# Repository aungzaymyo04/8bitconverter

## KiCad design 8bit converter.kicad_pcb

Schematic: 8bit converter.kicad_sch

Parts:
C1, C2: 10uf; CAP1608m
C19, C20, C21, C22, C23, C24, C25, C26, C27, C28, C29, C30, C31, C32, C33, C34, C35, C36: 0.1uF; CAP1608m
C37, C38: 10uF; CAP1608m
CN1: 10220-55G3PC
CN2: B4B-XH-A
D1: RB496EATR; Mouser Part Number 755-RB496EATR
D2, D3, D4, D5, D6, D7, D8, D9, D10: 1SS226
J1: CONBNC002
JP1: PAD_Short
MH1, MH2, MH3, MH4: HOLE_M3
PS1: MGS151205; Mouser Part Number 436-MGS151205
R2, R3, R5: 2.2k; REG1608m
R4, R6, R7, R8, R9, R10, R11, R12, R13: 10k; REG1608m
SW1: PN11SHNA03QE
U1, U2, U3, U4, U5, U6, U7, U8, U9: SN74LV1T34DBVR
U10: SC0915

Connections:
+3.3V: R2.2, R3.2, R5.2, U10.36 (3V3_OUT)
+5V: C19.2, C20.2, C21.2, C22.1, C23.2, C24.2, C25.1, C26.1, C27.2, C28.1, C29.2, C30.1, C31.2, C32.1, C33.2, C34.1, C35.2, C36.1, C37.1, C38.1, CN2.3, D1.4 (K_2), D2.2, D3.2, D4.2, D5.2, D6.2, D7.2, D8.2, D9.2, D10.2, PS1.4 (+VOUT), U1.5 (VCC), U2.5 (VCC), U3.5 (VCC), U4.5 (VCC), U5.5 (VCC), U6.5 (VCC), U7.5 (VCC), U8.5 (VCC), U9.5 (VCC), U10.39 (VSYS)
/+12V: C1.2, C2.2, CN1.9, CN1.19, PS1.3 (+VIN)
/SCL: CN2.2, R5.1, U10.32 (GP27)
/SDA: CN2.1, R3.1, U10.31 (GP26)
/o_5V_MUX0: CN1.14, D2.3, U1.4 (Y)
/o_5V_MUX1: CN1.4, D3.3, U2.4 (Y)
/o_5V_MUX2: CN1.13, D4.3, U3.4 (Y)
/o_5V_MUX3: CN1.3, D5.3, U4.4 (Y)
/o_5V_MUX4: CN1.12, D6.3, U5.4 (Y)
/o_5V_MUX5: CN1.2, D7.3, U6.4 (Y)
/o_5V_MUX6: CN1.11, D8.3, U7.4 (Y)
/o_5V_MUX7: CN1.1, D9.3, U8.4 (Y)
/o_MUX0: R8.1, U1.2 (A), U10.1 (GP0(UART_TX))
/o_MUX1: R6.1, U2.2 (A), U10.2 (GP1(UART_RX))
/o_MUX2: R4.1, U3.2 (A), U10.4 (GP2(SPI0_SCK))
/o_MUX3: R7.1, U4.2 (A), U10.5 (GP3(SPI0_TX))
/o_MUX4: R9.1, U5.2 (A), U10.6 (GP4(SPI0_RX)(UART1TX))
/o_MUX5: R10.1, U6.2 (A), U10.7 (GP5(SPI0CSn)(UART1RX))
/o_MUX6: R11.1, U7.2 (A), U10.9 (GP6(UART_TX))
/o_MUX7: R12.1, U8.2 (A), U10.10 (GP7(UART_RX))
/o_TRIG: R13.1, U9.2 (A), U10.11 (GP8(I2C1_SDA))
/o_TRIG_BNC: D10.3, J1.1, U9.4 (Y)
GND: C1.1, C2.1, C19.1, C20.1, C21.1, C22.2, C23.1, C24.1, C25.2, C26.2, C27.1, C28.2, C29.1, C30.2, C31.1, C32.2, C33.1, C34.2, C35.1, C36.2, C37.2, C38.2, CN1.7, CN1.17, CN1.MH1, CN1.MH2, CN2.4, D2.1, D3.1, D4.1, D5.1, D6.1, D7.1, D8.1, D9.1, D10.1, J1.2, J1.S1, J1.S2, JP1.1, MH1.1 (1_1), MH2.1 (1_1), MH3.1 (1_1), MH4.1 (1_1), PS1.2 (-VIN), PS1.6 (-VOUT), R4.2, R6.2, R7.2, R8.2, R9.2, R10.2, R11.2, R12.2, R13.2, SW1.1 (NO), U1.3 (GND), U2.3 (GND), U3.3 (GND), U4.3 (GND), U5.3 (GND), U6.3 (GND), U7.3 (GND), U8.3 (GND), U9.3 (GND), U10.3 (GND), U10.8 (GND), U10.13 (GND), U10.18 (GND), U10.23 (GND), U10.28 (GND), U10.33 (AGND), U10.38 (GND), U10.D2 (GND)
unnamed: D1.3 (A_2), U10.40 (VBUS)
unnamed: JP1.2, PS1.1 (RC)
unnamed: R2.1, SW1.2 (COM), U10.21 (GP16)

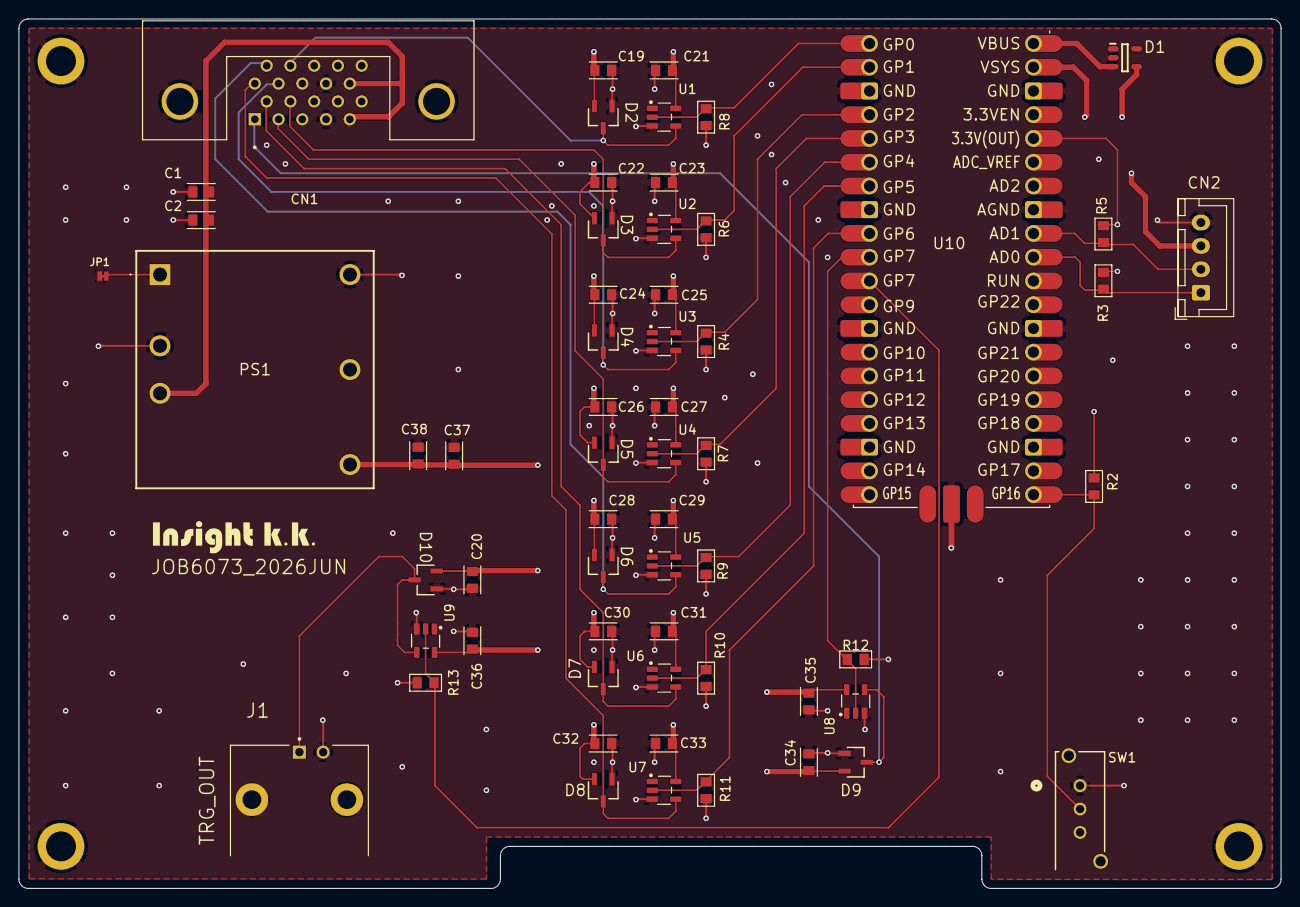
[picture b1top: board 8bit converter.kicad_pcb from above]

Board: 4 copper layers, 135.0 x 93.0 mm, 65 parts (0 on the bottom side), 27 nets.

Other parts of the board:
${REFERENCE}: ${VALUE}; Logo_S

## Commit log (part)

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2026-06-18 first_commit
2026-06-19 circuit_check
2026-06-22 PCB_edit
2026-06-22 PCB_check
